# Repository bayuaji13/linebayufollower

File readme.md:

pin motor 
kanan = 18,22
kiri = 15,16

pin sensor , layout
[kiri		] 	[kanan]
3 - 5 - 7 - 8 	10 - 11 - 12 - 13 
read paling gedhe dari terluar : 
[kiri		] 	[kanan]
3 - 5 - 7 - 8 	13 - 12 - 11 - 10

todos : kalibrasi sensor

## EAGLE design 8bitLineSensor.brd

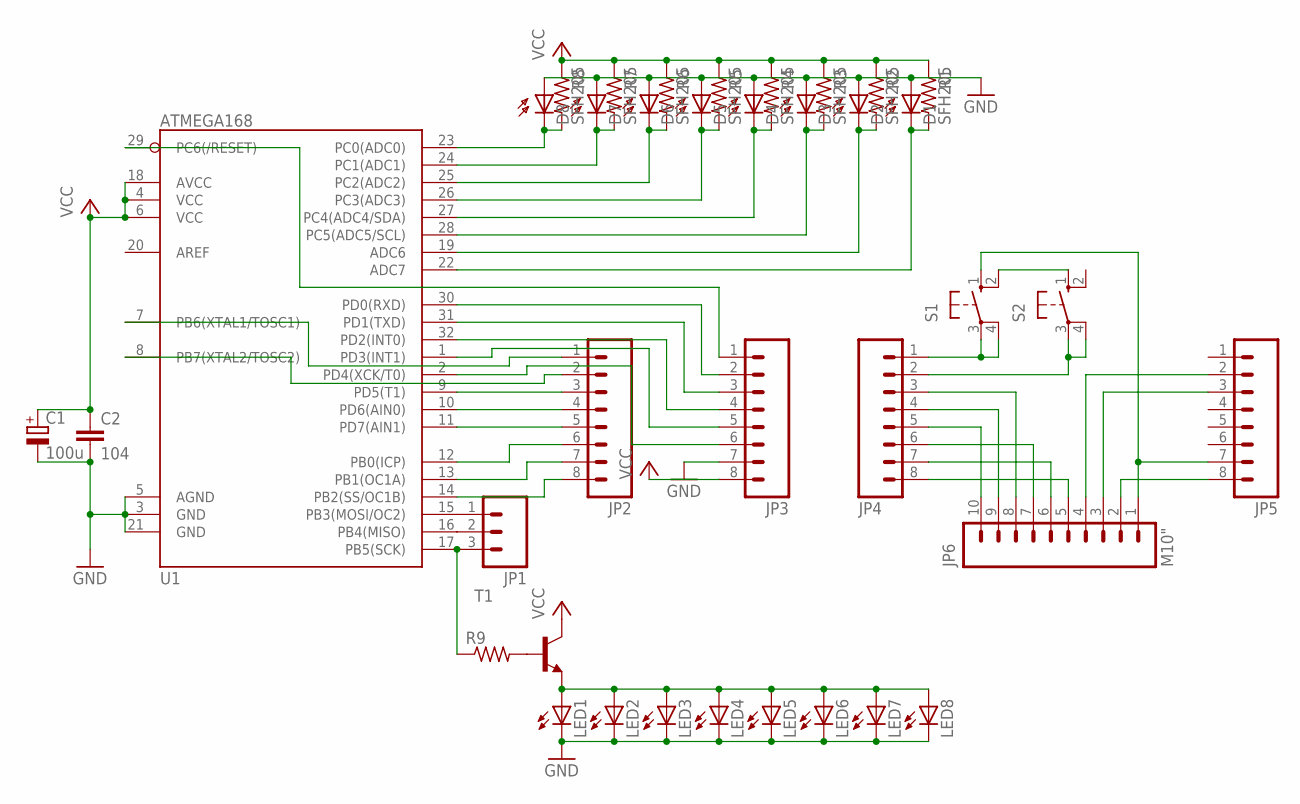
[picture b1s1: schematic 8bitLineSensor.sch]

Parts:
C1: 100u; E2,5-7
C2: 104; C0805
D1, D2, D3, D4, D5, D6, D7, D8: SFH205
JP1: M03PTH; 1X03
JP2, JP3, JP4, JP5: M08; 1X08
JP6: M10"; 1X10
LED1, LED2, LED3, LED4, LED5, LED6, LED7, LED8: LED5MM
R1, R2, R3, R4, R5, R6, R7, R8, R9: R-US_R0805; R0805
S1, S2: 10-XX; B3F-10XX
T1: MMBT2222ALT1-NPN-SOT23-BEC; SOT23-BEC
U1: ATMEGA168; TQFP32-08

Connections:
GND: C1.-, C2.2, D1.A, D2.A, D3.A, D4.A, D5.A, D6.A, D7.A, D8.A, JP3.7, LED1.K (C), LED2.K (C), LED3.K (C), LED4.K (C), LED5.K (C), LED6.K (C), LED7.K (C), LED8.K (C), U1.3 (GND), U1.5 (AGND), U1.21 (GND)
unnamed: R9.2, T1.B
unnamed: JP1.3, R9.1, U1.17 (PB5(SCK))
unnamed: JP2.6, U1.12 (PB0(ICP))
unnamed: D1.K (C), R1.2, U1.22 (ADC7)
unnamed: D2.K (C), R2.2, U1.19 (ADC6)
unnamed: JP2.7, U1.13 (PB1(OC1A))
unnamed: JP2.3, U1.9 (PD5(T1))
unnamed: JP2.4, U1.10 (PD6(AIN0))
unnamed: D3.K (C), R3.2, U1.28 (PC5(ADC5/SCL))
unnamed: JP2.5, U1.11 (PD7(AIN1))
unnamed: JP2.8, U1.14 (PB2(SS/OC1B))
unnamed: JP2.2, U1.8 (PB7(XTAL2/TOSC2))
unnamed: JP2.1, U1.7 (PB6(XTAL1/TOSC1))
unnamed: JP3.2, U1.30 (PD0(RXD))
unnamed: JP3.3, U1.31 (PD1(TXD))
unnamed: D4.K (C), R4.2, U1.27 (PC4(ADC4/SDA))
unnamed: D5.K (C), R5.2, U1.26 (PC3(ADC3))
unnamed: D6.K (C), R6.2, U1.25 (PC2(ADC2))
unnamed: D7.K (C), R7.2, U1.24 (PC1(ADC1))
unnamed: D8.K (C), R8.2, U1.23 (PC0(ADC0))
unnamed: JP3.4, U1.32 (PD2(INT0))
unnamed: JP3.5, U1.1 (PD3(INT1))
unnamed: JP3.6, U1.2 (PD4(XCK/T0))
unnamed: JP1.1, U1.15 (PB3(MOSI/OC2))
unnamed: JP1.2, U1.16 (PB4(MISO))
unnamed: LED1.A, LED2.A, LED3.A, LED4.A, LED5.A, LED6.A, LED7.A, LED8.A, T1.E
unnamed: JP5.7, JP6.1, S1.1 (S)
unnamed: JP3.1, U1.29 (PC6(/RESET))
unnamed: JP5.8, JP6.2
unnamed: JP4.6, JP6.7
unnamed: JP4.7, JP6.6
unnamed: JP4.3, JP6.8
unnamed: JP4.4, JP6.9
unnamed: JP4.5, JP6.10
unnamed: JP4.8, JP6.5
unnamed: JP5.2, JP6.4
unnamed: JP5.3, JP6.3
unnamed: JP4.1, S1.3, S1.4 (P1)
unnamed: JP4.2, S2.3, S2.4 (P1)
unnamed: S1.2 (S1), S2.1 (S)
VCC: C1.+, C2.1, JP3.8, R1.1, R2.1, R3.1, R4.1, R5.1, R6.1, R7.1, R8.1, T1.C, U1.4 (VCC), U1.6 (VCC), U1.18 (AVCC)

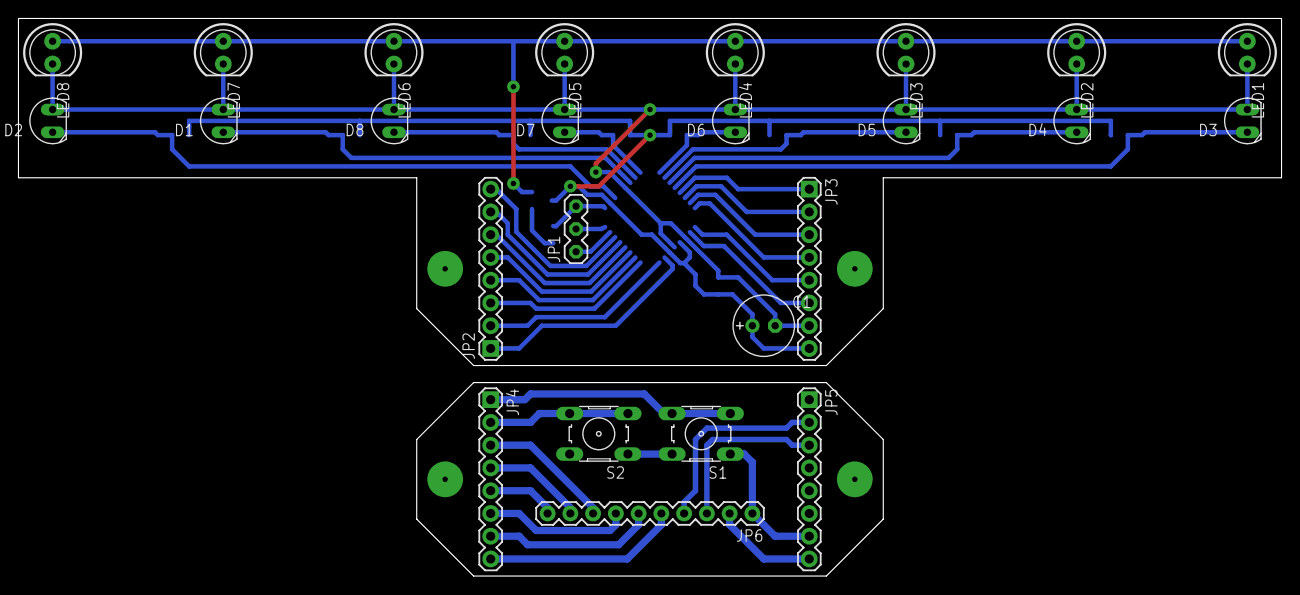
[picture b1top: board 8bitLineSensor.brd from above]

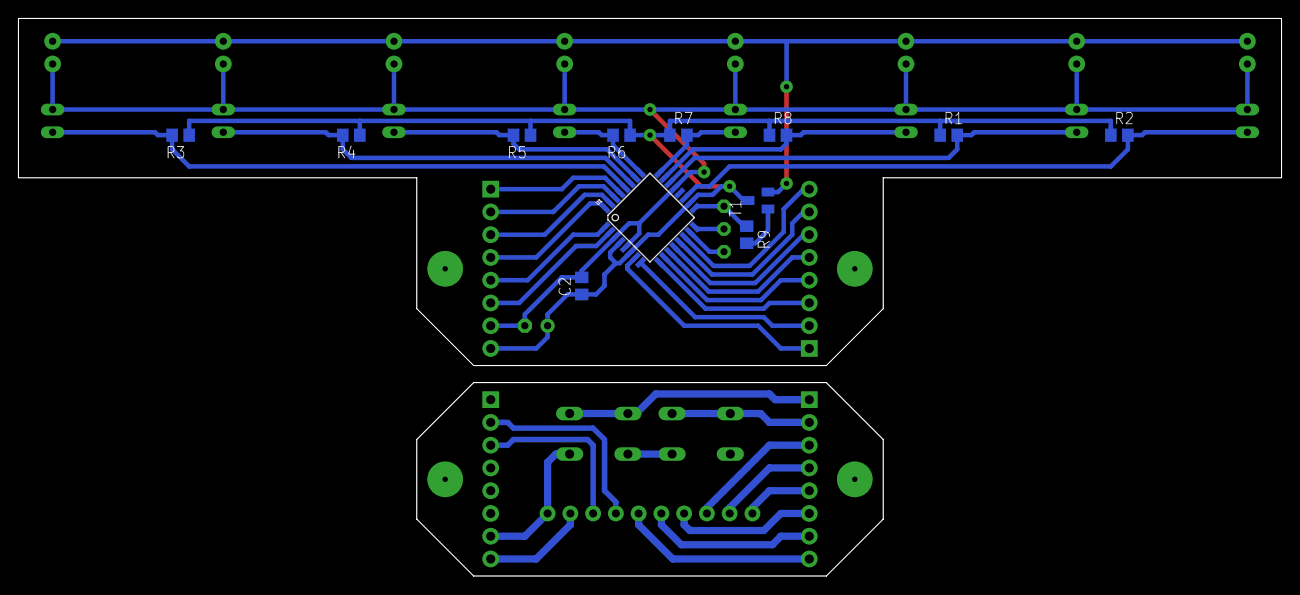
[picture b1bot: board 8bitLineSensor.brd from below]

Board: 2 copper layers, 141.0 x 62.2 mm, 37 parts (12 on the bottom side), 42 nets.

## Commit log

2017-02-02 :space_invader: Added .gitattributes
2017-02-04 class sensor (kurang konversi 16 ke 50)
2017-02-07 update sensor + robotize ke versi baru dan camel case
2017-02-13 tambahan readme buat sensor + coba gpio
2017-02-27 abstract + robotize

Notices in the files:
parts and their libraries:
SparkFun2010_04_13: Licensing: CC v3.0 Share-Alike You are welcome to use this library for commercial purposes.
